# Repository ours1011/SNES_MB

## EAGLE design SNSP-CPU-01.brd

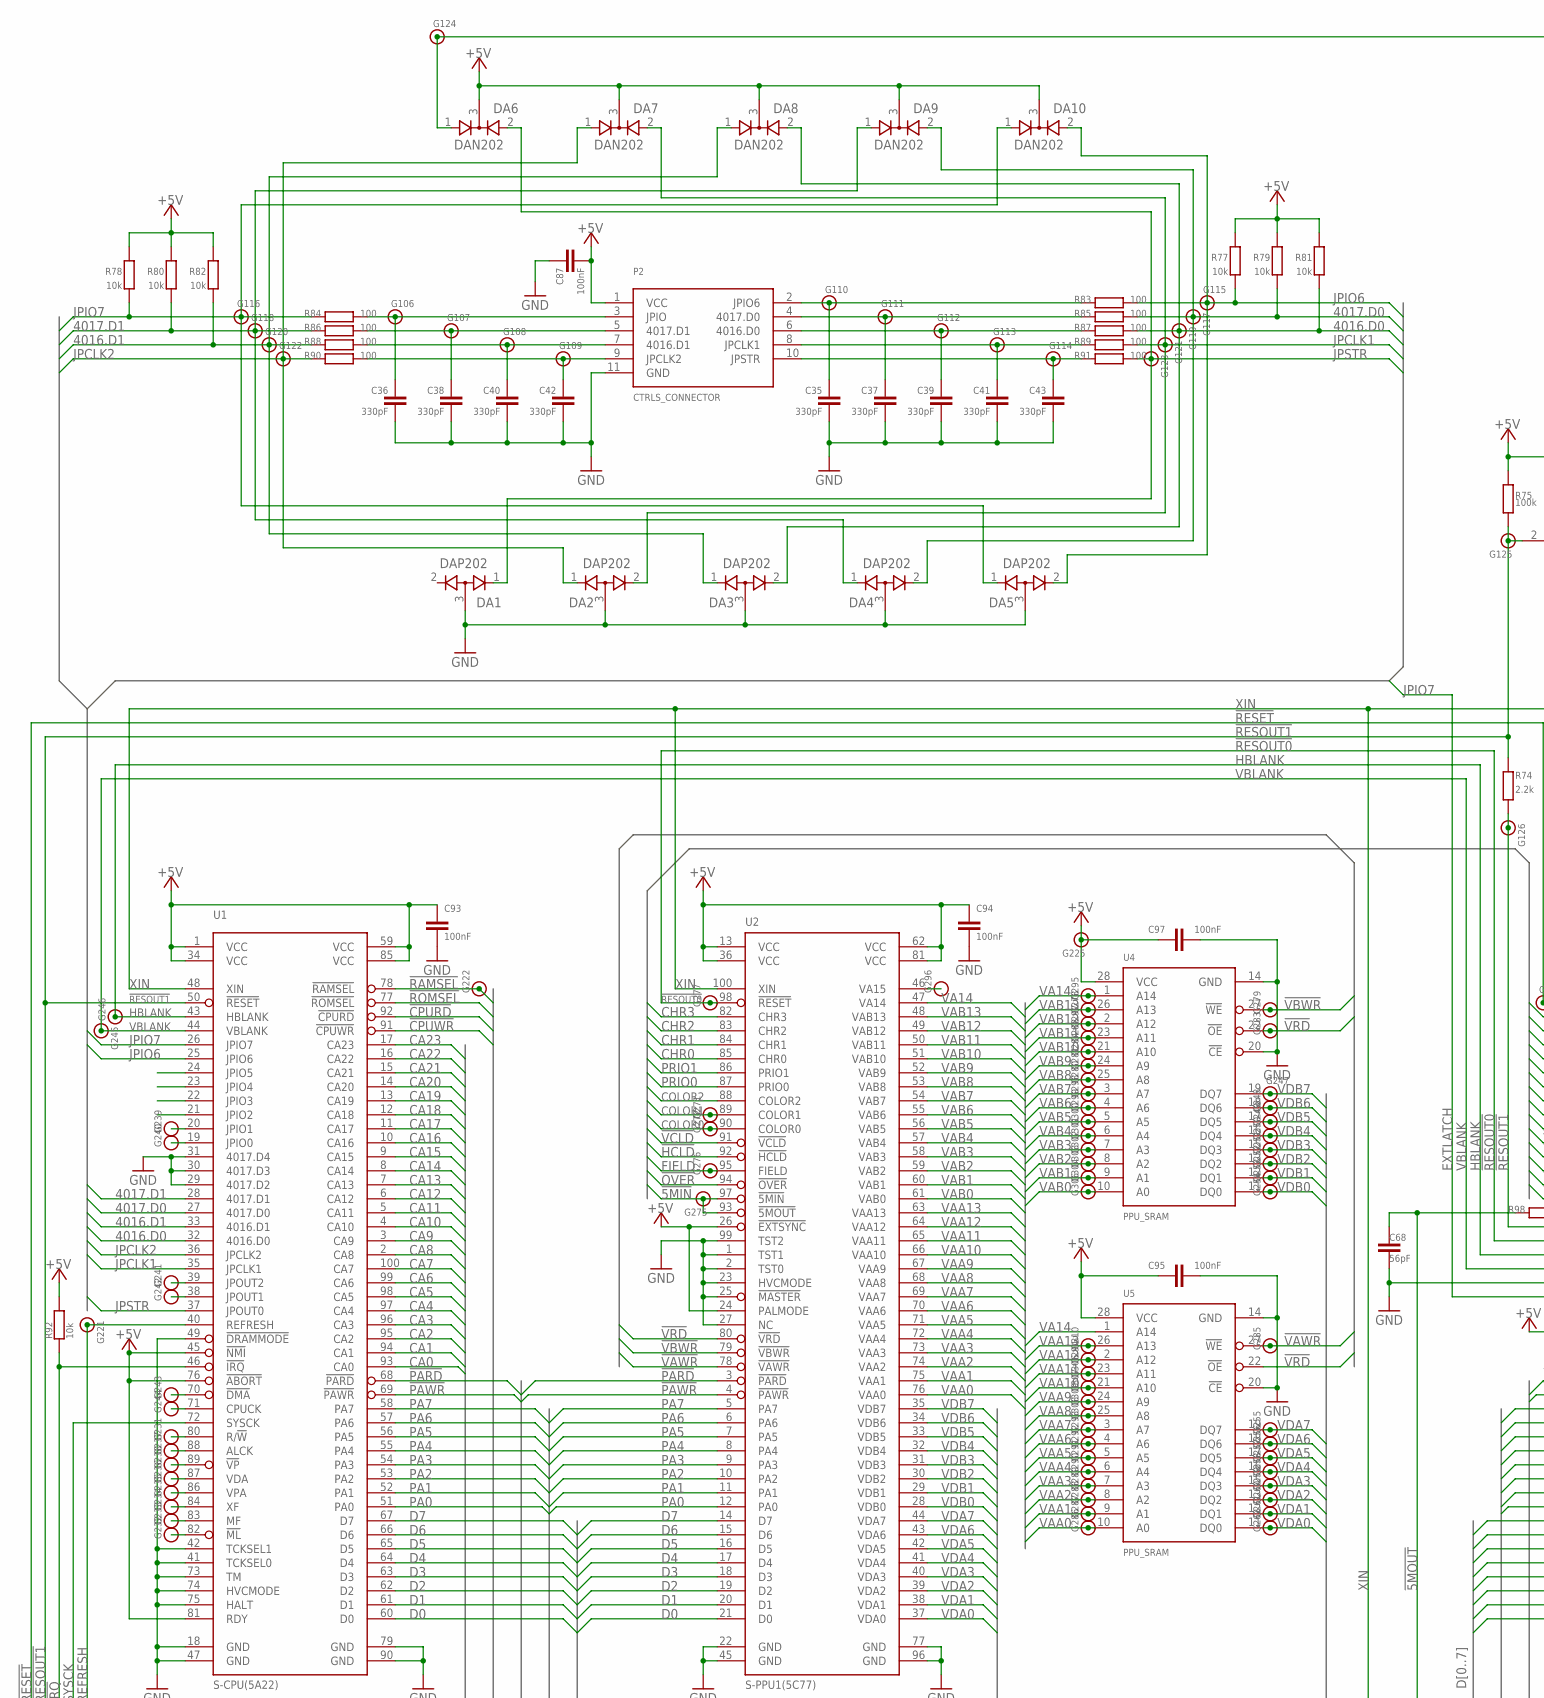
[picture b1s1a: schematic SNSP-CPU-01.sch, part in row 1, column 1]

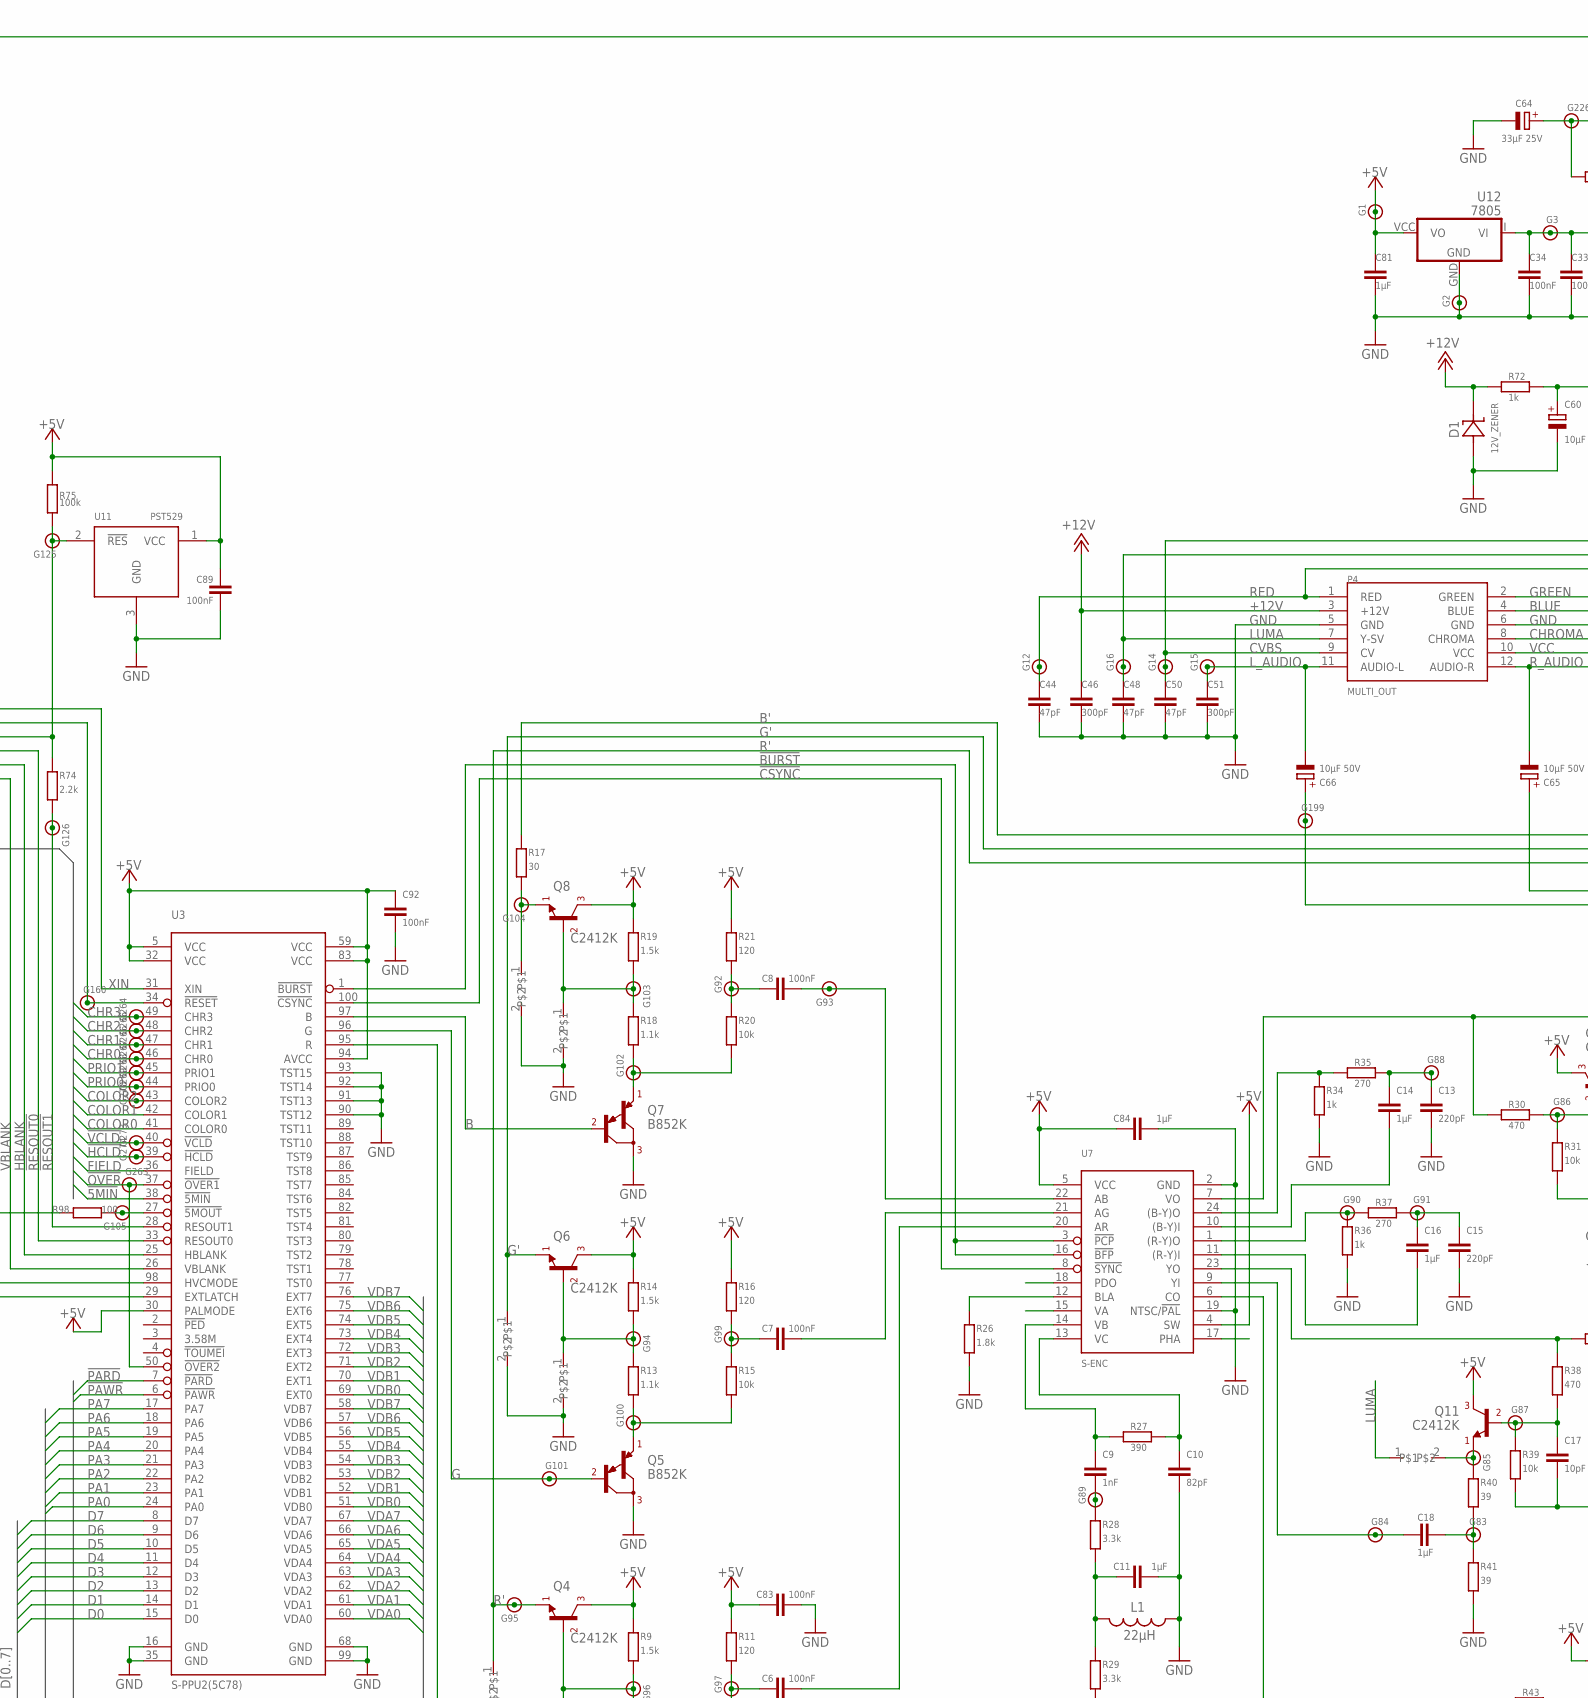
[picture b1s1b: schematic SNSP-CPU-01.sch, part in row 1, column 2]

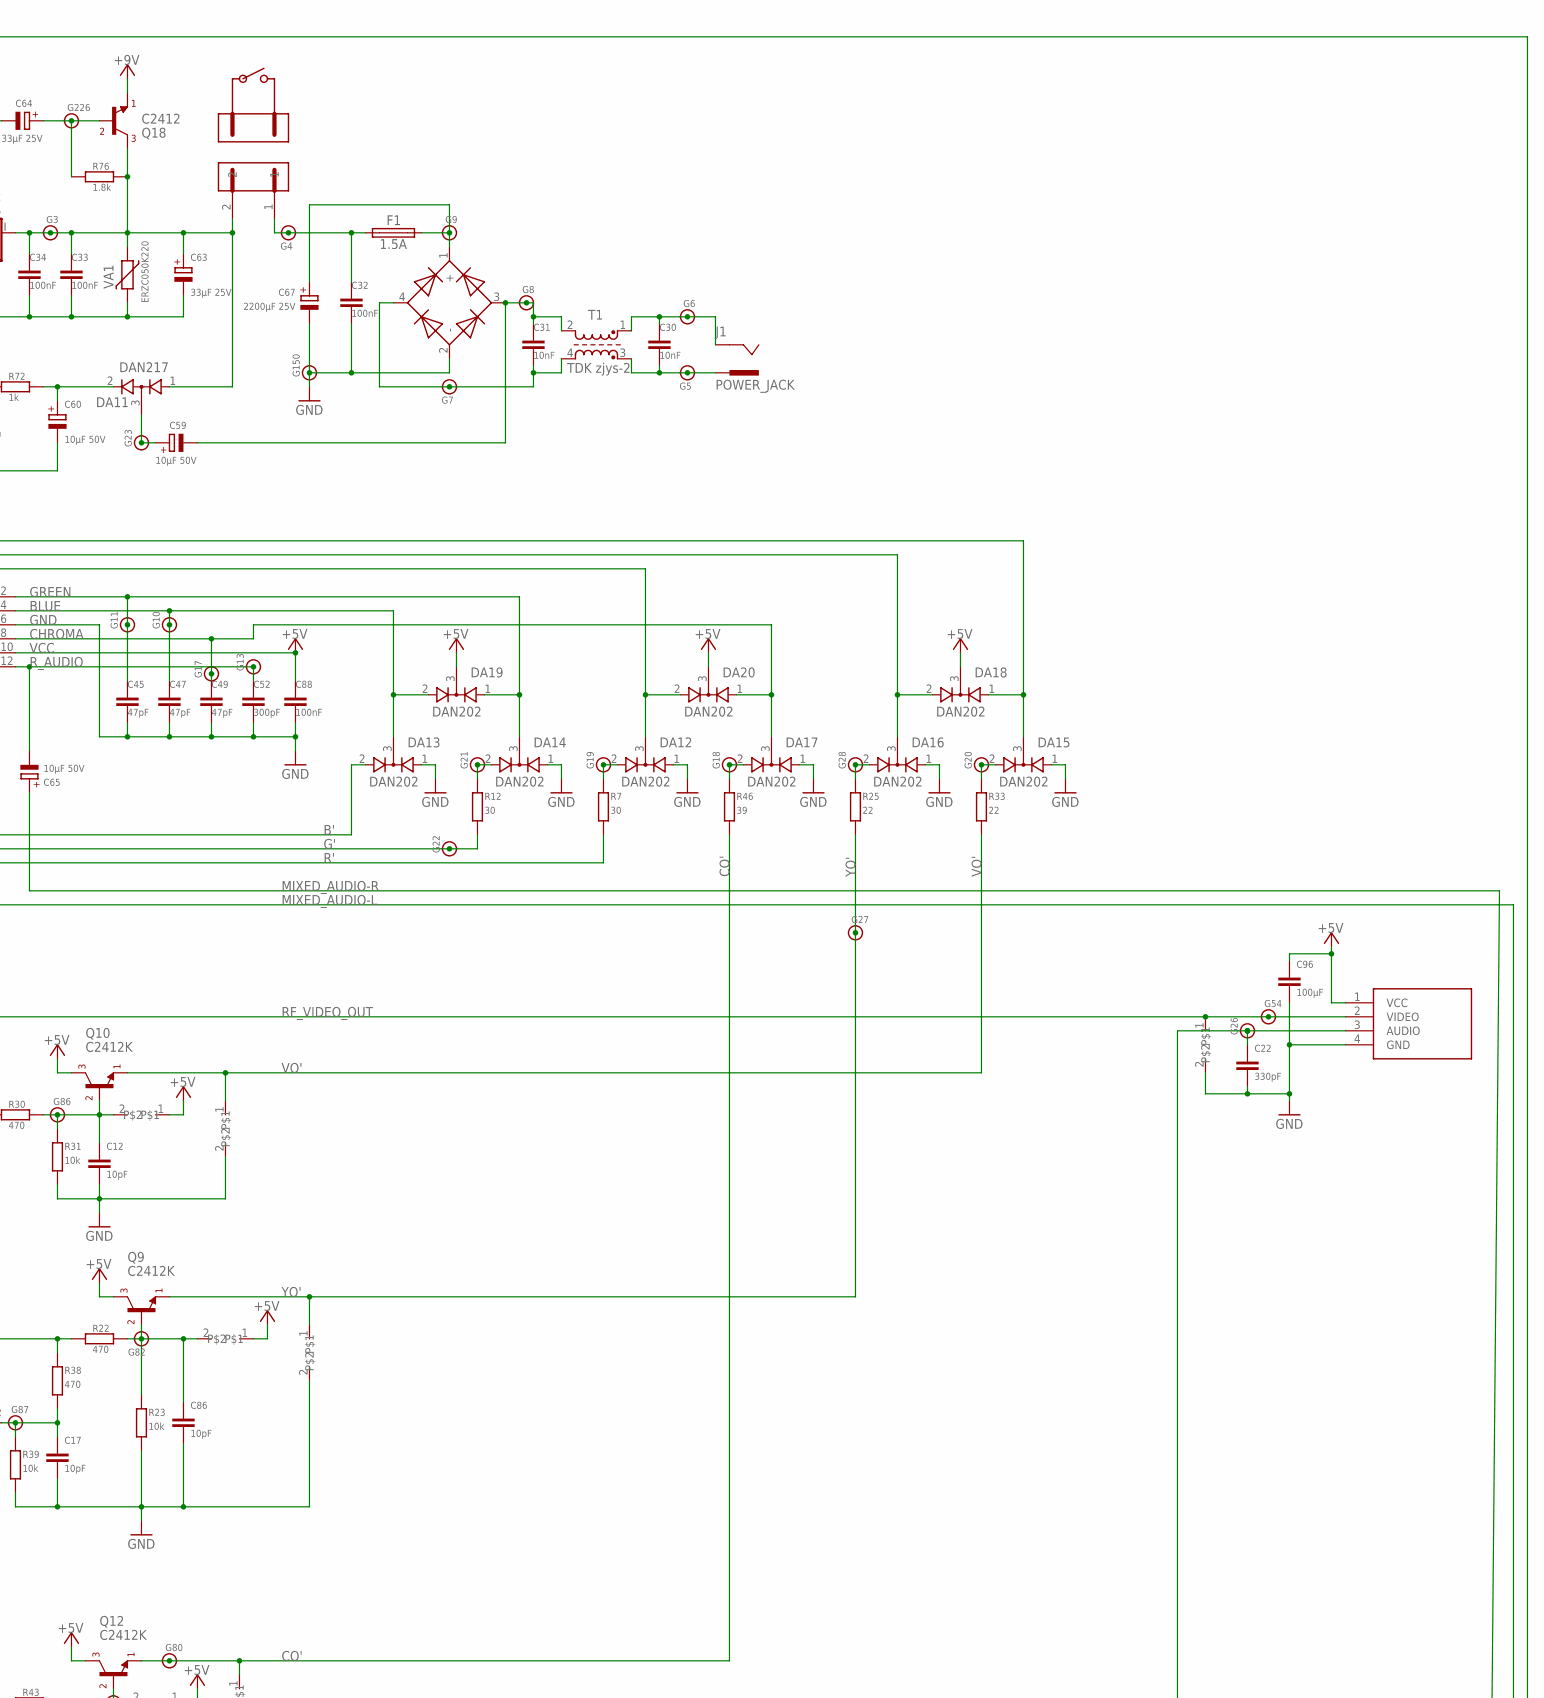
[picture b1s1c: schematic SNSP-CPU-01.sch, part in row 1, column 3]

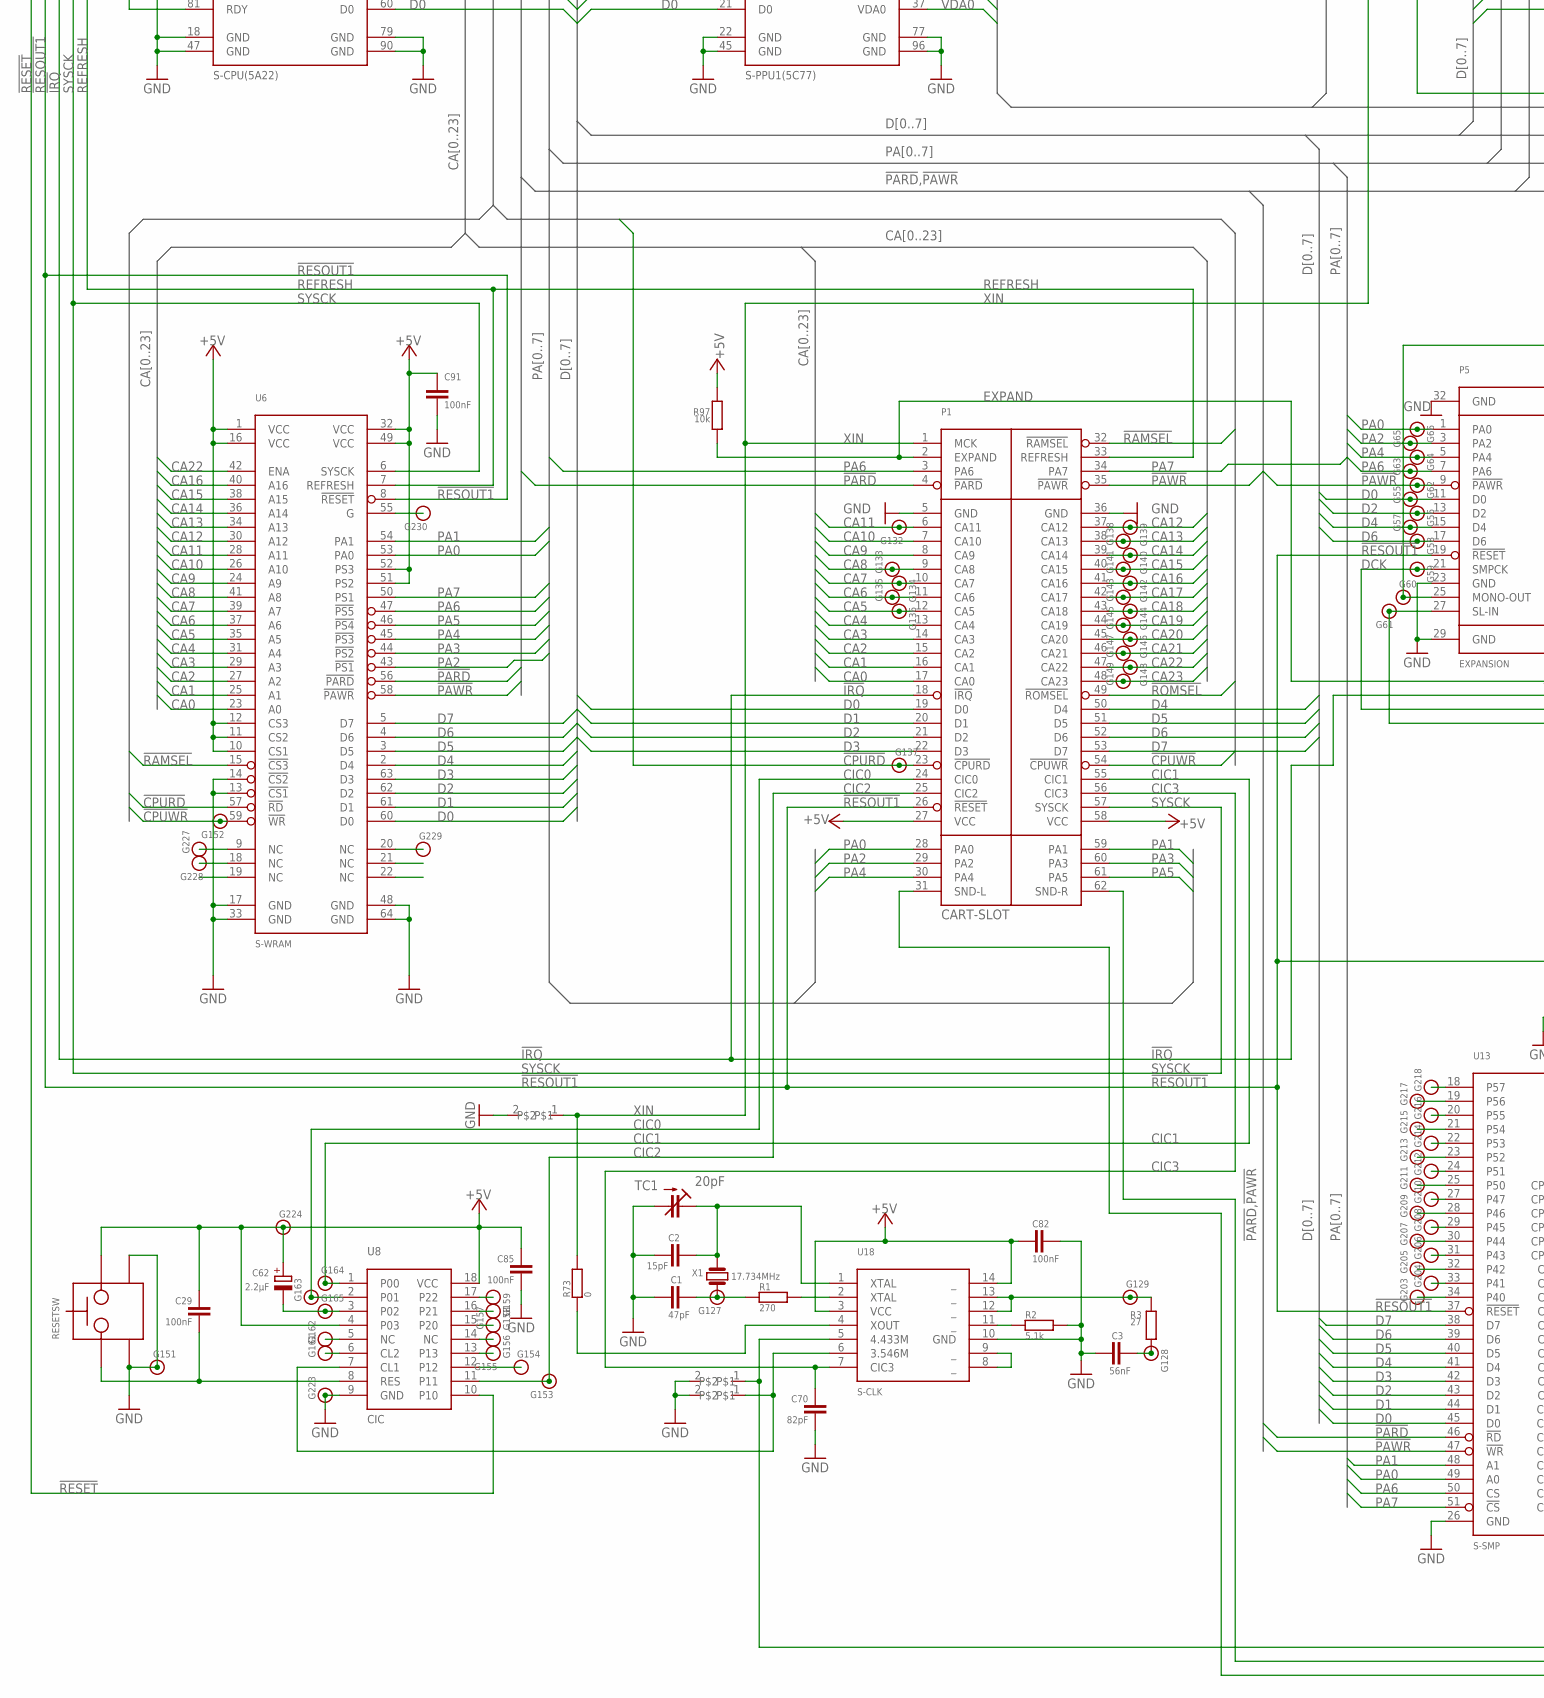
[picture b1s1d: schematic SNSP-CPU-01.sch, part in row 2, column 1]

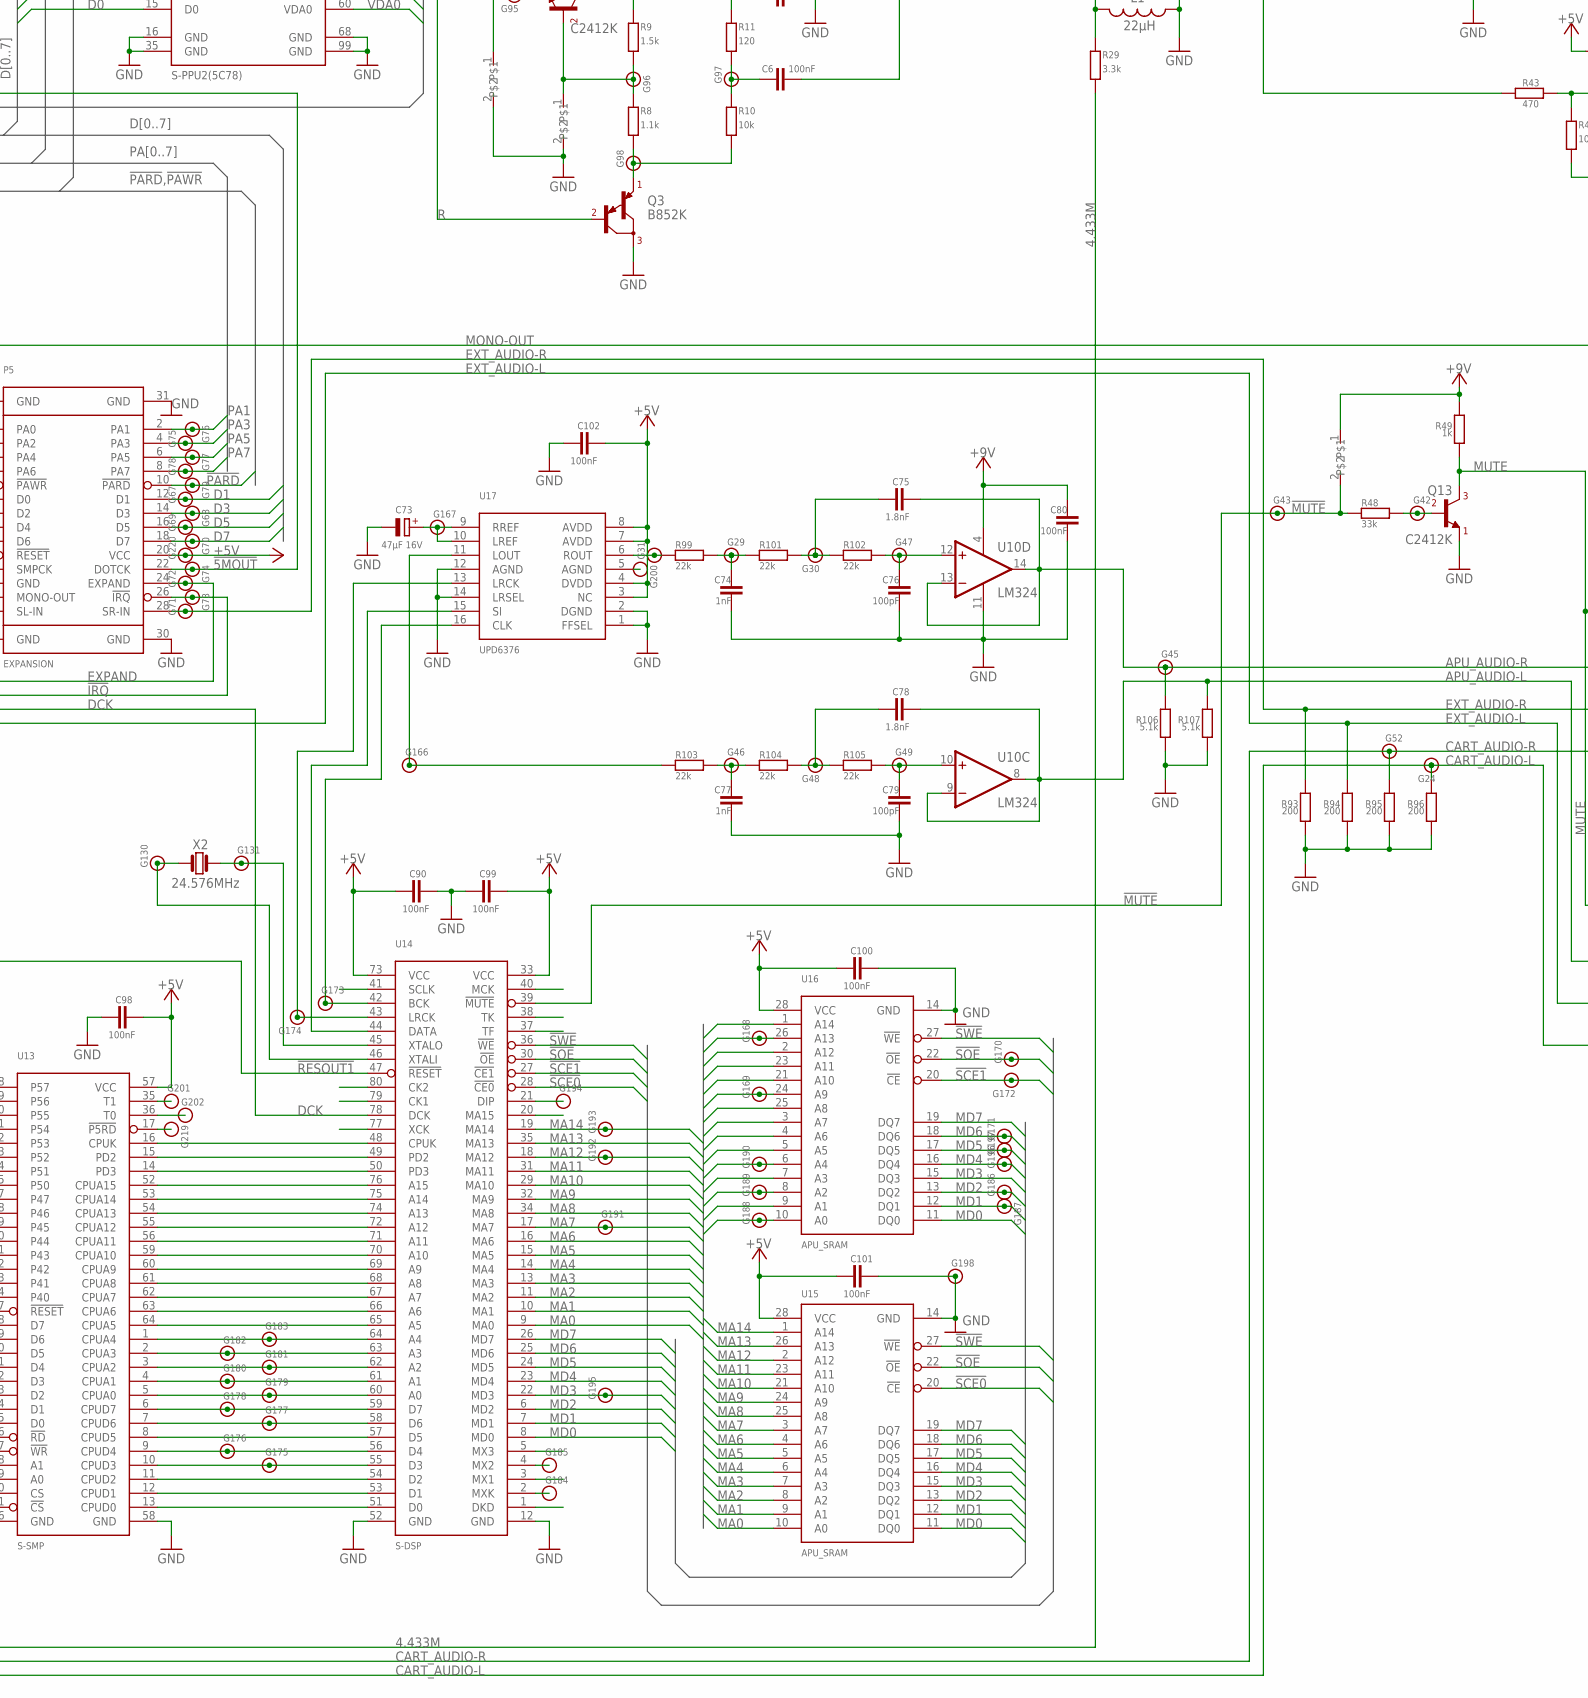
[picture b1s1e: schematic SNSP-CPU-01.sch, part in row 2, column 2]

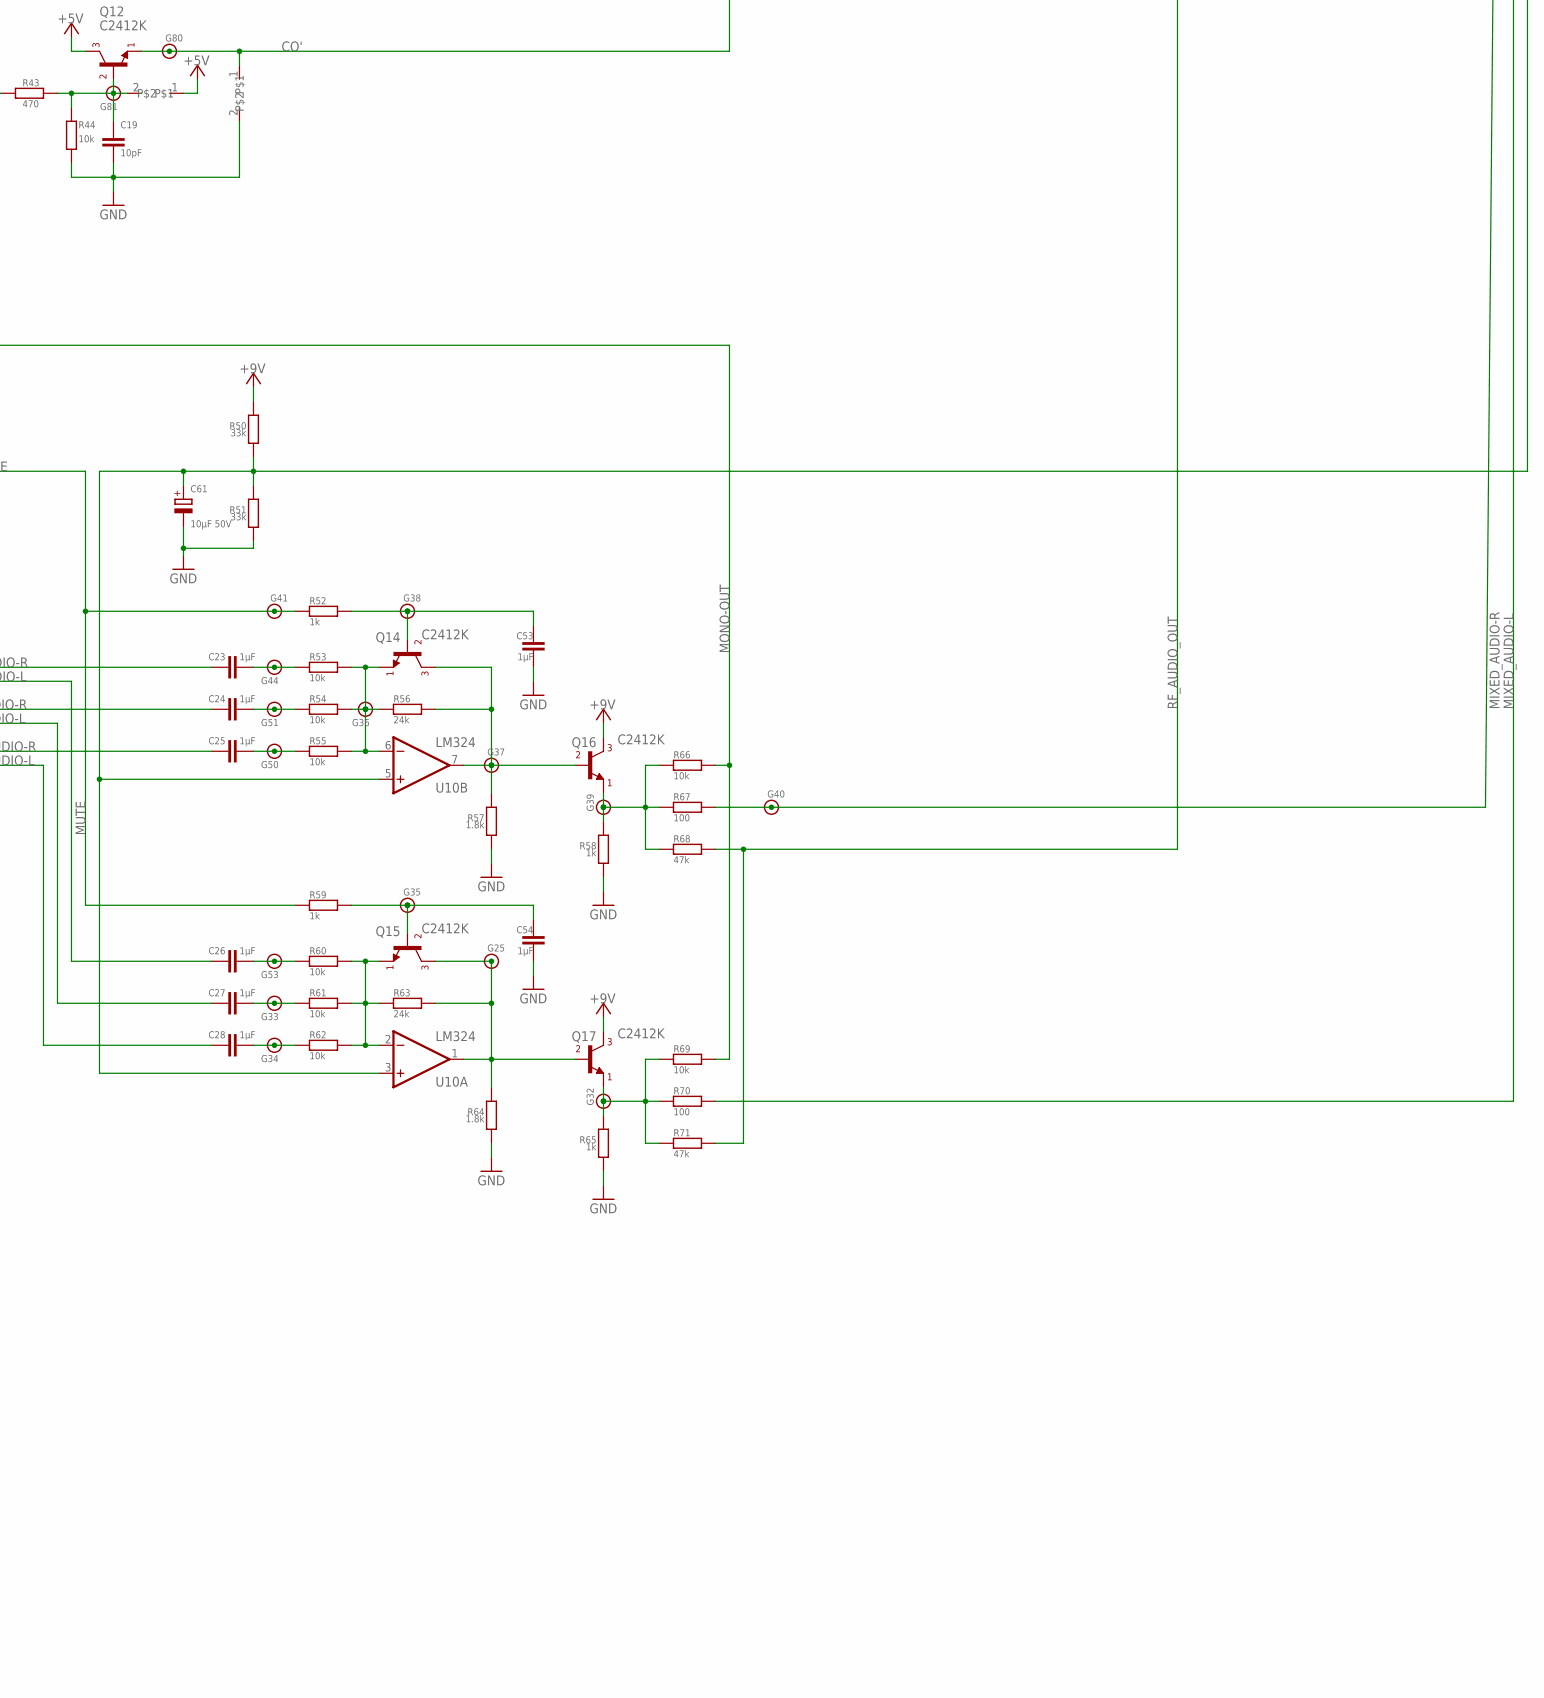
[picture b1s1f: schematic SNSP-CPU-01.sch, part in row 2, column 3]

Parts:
C1, C44, C45, C47, C48, C49, C50: 47pF; 0805
C2: 15pF; 0805
C3: 56nF; 0805
C4, C5, C69: EMPTY_0805; 0805_EMPTY
C6, C7, C8, C29, C32, C33, C34, C80, C82, C83, C85, C87, C88, C89, C90, C91, C92, C93, C94, C95, C97, C98, C99, C100, C101, C102: 100nF; 0805
C9, C74, C77: 1nF; 0805
C10, C70: 82pF; 0805
C11, C14, C16, C18, C23, C24, C25, C26, C27, C28, C53, C54, C81, C84: 1µF; 0805
C12, C17, C19, C86: 10pF; 0805
C13, C15: 220pF; 0805
C22, C35, C36, C37, C38, C39, C40, C41, C42, C43: 330pF; 0805
C30, C31: 10nF; 0805
C46, C51, C52: 300pF; 0805
C59, C60, C61, C65, C66: 10µF 50V; CAPA_POL_SMD_6.5
C62: 2.2µF; CAPA_POL_SMD_4.3
C63, C64: 33µF 25V; CAPA_POL_SMD_6.5
C67: 2200µF 25V; CAPA_POL
C68: 56pF; 0805
C73: 47µF 16V; CAPA_POL_SMD_6.5
C75, C78: 1.8nF; 0805
C76, C79: 100pF; 0805
C96: 100µF; 0805
D1: 12V_ZENER; SOT23
DA1, DA2, DA3, DA4, DA5: DAP202; SOT23
DA6, DA7, DA8, DA9, DA10, DA12, DA13, DA14, DA15, DA16, DA17, DA18, DA19, DA20: DAN202; SOT23
DA11: DAN217; SOT23
DB1: RECTIFIER
E1, E2, E3: EMPTY_0805; 0805_EMPTY
F1: 1.5A; FUSE
G1, G2, G3, G4, G5, G6, G7, G8, G9, G10, G11, G12, G13, G14, G15, G16, G17, G18, G19, G20, G21, G22, G23, G24, G25, G26, G27, G28, G29, G30, G31, G32, G33, G34, G35, G36, G37, G38, G39, G40, G41, G42, G43, G44, G45, G46, G47, G48, G49, G50, G51, G52, G53, G54, G55, G56, G57, G58, G59, G60, G61, G62, G63, G64, G65, G66, G67, G68, G69, G70, G71, G72, G73, G74, G75, G76, G77, G78, G79, G80, G81, G82, G83, G84, G85, G86, G87, G88, G89, G90, G91, G92, G93, G94, G95, G96, G97, G98, G99, G100, G101, G102, G103, G104, G105, G106, G107, G108, G109, G110, G111, G112, G113, G114, G115, G116, G117, G118, G119, G120, G121, G122, G123, G124, G125, G126, G127, G128, G129, G130, G131, G132, G133, G134, G135, G136, G137, G138, G139, G140, G141, G142, G143, G144, G145, G146, G147, G148, G149, G150, G151, G152, G153, G154, G155, G156, G157, G158, G159, G160, G161, G162, G163, G164, G165, G166, G167, G168, G169, G170, G171, G172, G173, G174, G175, G176, G177, G178, G179, G180, G181, G182, G183, G184, G185, G186, G187, G188, G189, G190, G191, G192, G193, G194, G195, G196, G197, G198, G199, G200, G201, G202, G203, G204, G205, G206, G207, G208, G209, G210, G211, G212, G213, G214, G215, G216, G217, G218, G219, G220, G221, G222, G223, G224, G225, G226, G227, G228, G229, G230, G231, G232, G233, G234, G235, G236, G237, G238, G239, G240, G241, G242, G243, G244, G245, G246, G247, G248, G249, G250, G251, G252, G253, G254, G255, G256, G257, G258, G259, G260, G261, G262, G263, G264, G265, G266, G267, G268, G269, G270, G271, G272, G273, G274, G275, G276, G277, G278, G279, G280, G281, G282, G283, G284, G285, G286, G287, G288, G289, G290, G291, G292, G293, G294, G295, G296, G297, G298, G299, G300, G301, G302, G303, G304, G305, G306, G307, G308, G309, G310: TEST
J1: POWER_JACK
J2: RF_MODULATOR; RF
L1: 22µH; INDUCTOR
P1: CART-SLOT
P2: CTRLS_CONNECTOR
P3: PWR_SW
P4: MULTI_OUT
P5: EXPANSION
Q3, Q5, Q7: B852K; SOT23
Q4, Q6, Q8, Q9, Q10, Q11, Q12, Q13, Q14, Q15, Q16, Q17: C2412K; SOT23
Q18: C2412; SOT23
R1, R35, R37: 270; 0805
R2, R106, R107: 5.1k; 0805
R3: 27; 0805
R4, R5, R6, R24, R32, R42, R45, R47, R108, R109, R110, R111: EMPTY_0805; 0805_EMPTY
R7, R12, R17: 30; 0805
R8, R13, R18: 1.1k; 0805
R9, R14, R19: 1.5k; 0805
R10, R15, R20, R23, R31, R39, R44, R53, R54, R55, R60, R61, R62, R66, R69, R77, R78, R79, R80, R81, R82, R92, R97: 10k; 0805
R11, R16, R21: 120; 0805
R22, R30, R38, R43: 470; 0805
R25, R33: 22; 0805
R26, R57, R64, R76: 1.8k; 0805
R27: 390; 0805
R28, R29: 3.3k; 0805
R34, R36, R49, R52, R58, R59, R65, R72: 1k; 0805
R40, R41, R46: 39; 0805
R48, R50, R51: 33k; 0805
R56, R63: 24k; 0805
R67, R70, R83, R84, R85, R86, R87, R88, R89, R90, R91, R98: 100; 0805
R68, R71: 47k; 0805
R73: 0; 0805
R74: 2.2k; 0805
R75: 100k; 0805
R93, R94, R95, R96: 200; 0805
R99, R101, R102, R103, R104, R105: 22k; 0805
RESETSW: RESET_SW
T1: TDK zjys-2; TRANSF
TC1: 20pF; C-TRIMM
U1: S-CPU(5A22); 100QFP0.65
U2: S-PPU1(5C77); 100QFP0.65
U3: S-PPU2(5C78); 100QFP0.65
U4, U5: PPU_SRAM; SO28L
U6: S-WRAM; SSO64
U7: S-ENC; SO24
U8: CIC
U10: LM324; SO14
U11: PST529
U12: 7805; TO220V
U13: S-SMP; 64QFP1.00
U14: S-DSP; 80QFP0.8
U15, U16: APU_SRAM; SO28W
U17: UPD6376; SO16
U18: S-CLK; SO14L
VA1: ERZC050K220; VARISTOR
X1: 17.734MHz; XTAL_MAIN
X2: 24.576MHz; XTAL_S-DSP

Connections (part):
4.433M: C69.1, R29.1, U18.5 (4.433M)
4016.D0: DA3.2, DA8.2 (1), G119.T, R81.1, R87.2, U1.32 (4016.D0)
4016.D1: DA3.1, DA8.1 (2), G120.T, R82.1, R88.1, U1.33 (4016.D1)
4017.D0: DA4.2, DA9.2 (1), G117.T, R79.1, R85.2, U1.27 (4017.D0)
4017.D1: DA4.1, DA9.1 (2), G118.T, R80.1, R86.1, U1.28 (4017.D1)
!5MIN: G275.T, U2.93 (!5MOUT), U2.97 (!5MIN), U3.38 (!5MIN)
!5MOUT: C68.1, G74.T, P5.22 (DOTCK), R98.1
!BURST: U3.1 (!BURST), U7.3 (!PCP), U7.16 (!BFP)
!CPURD: G137.T, P1.23 (!CPURD), U1.92 (!CPURD), U6.57 (!RD)
!CPUWR: G152.T, P1.54 (!CPUWR), U1.91 (!CPUWR), U6.59 (!WR)
!CSYNC: U3.100 (!CSYNC), U7.8 (!SYNC)
!HCLD: G274.T, U2.92 (!HCLD), U3.39 (!HCLD)
!IRQ: G73.T, P1.18 (!IRQ), P5.26 (!IRQ), R92.1, U1.46 (!IRQ)
!MUTE: G43.T, R47.2, R48.1, U14.39 (!MUTE)
!OVER: G263.T, U2.94 (!OVER), U3.37 (!OVER1), U3.50 (!OVER2)
!PARD: G79.T, P1.4 (!PARD), P5.10 (!PARD), U1.68 (!PARD), U2.3 (!PARD), U3.7 (!PARD), U6.56 (!PARD), U13.46 (!RD)
!PAWR: G62.T, P1.35 (!PAWR), P5.9 (!PAWR), U1.69 (!PAWR), U2.4 (!PAWR), U3.6 (!PAWR), U6.58 (!PAWR), U13.47 (!WR)
!RAMSEL: G222.T, P1.32 (!RAMSEL), U1.78 (!RAMSEL), U6.15 (!CS3)
!RESET: G160.T, U3.34 (!RESET), U8.10
!RESOUT0: G277.T, U2.98 (!RESET), U3.33 (RESOUT0)
!RESOUT1: G125.T, P1.26 (!RESET), P5.19 (!RESET), R74.2, R75.1, U1.50 (!RESET), U6.8 (!RESET), U11.2 (!RES), U13.37 (!RESET), U14.47 (!RESET)
!ROMSEL: P1.49 (!ROMSEL), U1.77 (!ROMSEL)
!SCE0: U14.28 (!CE0), U15.20 (!CE)
!SCE1: G172.T, U14.27 (!CE1), U16.20 (!CE)
!SOE: G170.T, U14.30 (!OE), U15.22 (!OE), U16.22 (!OE)
!SWE: U14.36 (!WE), U15.27 (!WE), U16.27 (!WE)
!VAWR: G285.T, U2.78 (!VAWR), U5.27 (!WE)
!VBWR: G279.T, U2.79 (!VBWR), U4.27 (!WE)
!VCLD: G273.T, U2.91 (!VCLD), U3.40 (!VCLD)
!VRD: G283.T, U2.80 (!VRD), U4.22 (!OE), U5.22 (!OE)
+9V: C80.2, Q16.3, Q17.3, Q18.2 (1), R47.1, R49.1, R50.1, U10.4 (V+)
+12V: C46.2, D1.3, P4.3 (+12V), R72.2
/RESOUT1: G126.T, R74.1, U3.28 (RESOUT1)
APU_AUDIO-L: C26.1, C78.2, R107.1, U10.8 (OUT), U10.9 (-IN)
APU_AUDIO-R: C23.1, C75.2, G45.T, R106.1, U10.13 (-IN), U10.14 (OUT)
B: Q7.1 (2), U3.97 (B)
B': DA13.2 (1), R17.2
BLUE: C47.2, DA13.3, DA19.2 (1), G10.T, P4.4 (BLUE)
CA0: P1.17 (CA0), U1.93 (CA0), U6.23 (A0)
CA1: P1.16 (CA1), U1.94 (CA1), U6.25 (A1)
CA2: P1.15 (CA2), U1.95 (CA2), U6.27 (A2)
CA3: P1.14 (CA3), U1.96 (CA3), U6.29 (A3)
CA4: P1.13 (CA4), U1.97 (CA4), U6.31 (A4)
CA5: G136.T, P1.12 (CA5), U1.98 (CA5), U6.35 (A5)
CA6: G135.T, P1.11 (CA6), U1.99 (CA6), U6.37 (A6)
CA7: G134.T, P1.10 (CA7), U1.100 (CA7), U6.39 (A7)
CA8: G133.T, P1.9 (CA8), U1.2 (CA8), U6.41 (A8)
CA9: P1.8 (CA9), U1.3 (CA9), U6.24 (A9)
CA10: P1.7 (CA10), U1.4 (CA10), U6.26 (A10)
CA11: G132.T, P1.6 (CA11), U1.5 (CA11), U6.28 (A11)
CA12: G139.T, P1.37 (CA12), U1.6 (CA12), U6.30 (A12)
CA13: G138.T, P1.38 (CA13), U1.7 (CA13), U6.34 (A13)
CA14: G140.T, P1.39 (CA14), U1.8 (CA14), U6.36 (A14)
CA15: G141.T, P1.40 (CA15), U1.9 (CA15), U6.38 (A15)
CA16: G142.T, P1.41 (CA16), U1.10 (CA16), U6.40 (A16)
CA17: G143.T, P1.42 (CA17), U1.11 (CA17)
CA18: G144.T, P1.43 (CA18), U1.12 (CA18)
CA19: G145.T, P1.44 (CA19), U1.13 (CA19)
CA20: G146.T, P1.45 (CA20), U1.14 (CA20)
CA21: G147.T, P1.46 (CA21), U1.15 (CA21)
CA22: G148.T, P1.47 (CA22), U1.16 (CA22), U6.42 (ENA)
CA23: G149.T, P1.48 (CA23), U1.17 (CA23)
CART_AUDIO-L: C28.1, G24.T, P1.31 (SND-L), R96.1
CART_AUDIO-R: C25.1, G52.T, P1.62 (SND-R), R95.1
CHR0: G267.T, U2.85 (CHR0), U3.46 (CHR0)
CHR1: G266.T, U2.84 (CHR1), U3.47 (CHR1)
CHR2: G265.T, U2.83 (CHR2), U3.48 (CHR2)
CHR3: G264.T, U2.82 (CHR3), U3.49 (CHR3)
CHROMA: C49.2, DA17.3, DA20.1 (2), G17.T, P4.8 (CHROMA)
CIC0: G163.T, P1.24 (CIC0), U8.2 (P01)
CIC1: G164.T, P1.55 (CIC1), U8.1 (P00)
CIC2: G153.T, P1.25 (CIC2), U8.11
CIC3: C70.1, P1.56 (CIC3), U18.7 (CIC3)
CO': G80.T, Q12.2 (1), R45.1, R46.1
COLOR0: G272.T, U2.90 (COLOR0), U3.41 (COLOR0)
COLOR1: G271.T, U2.89 (COLOR1), U3.42 (COLOR1)
COLOR2: G270.T, U2.88 (COLOR2), U3.43 (COLOR2)
CVBS: C50.2, DA15.3, DA18.1 (2), G14.T, P4.9 (CV)
D0: G55.T, P1.19 (D0), P5.11 (D0), U1.60 (D0), U2.21 (D0), U3.15 (D0), U6.60 (D0), U13.45 (D0)
D1: G67.T, P1.20 (D1), P5.12 (D1), U1.61 (D1), U2.20 (D1), U3.14 (D1), U6.61 (D1), U13.44 (D1)
D2: G56.T, P1.21 (D2), P5.13 (D2), U1.62 (D2), U2.19 (D2), U3.13 (D2), U6.62 (D2), U13.43 (D2)
D3: G68.T, P1.22 (D3), P5.14 (D3), U1.63 (D3), U2.18 (D3), U3.12 (D3), U6.63 (D3), U13.42 (D3)
D4: G57.T, P1.50 (D4), P5.15 (D4), U1.64 (D4), U2.17 (D4), U3.11 (D4), U6.2 (D4), U13.41 (D4)
D5: G69.T, P1.51 (D5), P5.16 (D5), U1.65 (D5), U2.16 (D5), U3.10 (D5), U6.3 (D5), U13.40 (D5)
D6: G58.T, P1.52 (D6), P5.17 (D6), U1.66 (D6), U2.15 (D6), U3.9 (D6), U6.4 (D6), U13.39 (D6)
D7: G70.T, P1.53 (D7), P5.18 (D7), U1.67 (D7), U2.14 (D7), U3.8 (D7), U6.5 (D7), U13.38 (D7)
DCK: G59.T, P5.21 (SMPCK), U14.78 (DCK)
EXPAND: G72.T, P1.2 (EXPAND), P5.24 (EXPAND), R97.1
EXT_AUDIO-L: C27.1, G61.T, P5.27 (SL-IN), R94.1
EXT_AUDIO-R: C24.1, G71.T, P5.28 (SR-IN), R93.1
FIELD: G276.T, U2.95 (FIELD), U3.36 (FIELD)
G: G101.T, Q5.1 (2), U3.96 (G)
G': G22.T, Q6.2 (1), R5.1, R12.1
GND: C1.2, C2.2, C3.1, C4.2, C5.2, C10.2, C11.2, C12.2, C13.1, C15.1, C17.2, C19.2, C22.2, C32.1, C33.1, C34.1, C35.2, C36.2, C37.2, C38.2, C39.2, C40.2, C41.2, C42.2, C43.2, C44.1, C45.1, C46.1, C47.1, C48.1, C49.1, C50.1, C51.1, C52.1, C53.1, C54.1, C60.-, C61.-, C63.-, C64.-, C67.-, C68.2, C69.2, C70.2, C73.-, C74.1, C76.1, C77.1, C79.1, C80.1, C81.1, C82.2, C83.2, C84.2, C85.2, C86.2, C87.1, C88.1, C89.2, C90.2, C91.2, C92.2, C93.2, C94.2, C95.2, C96.2, C97.2, C98.1, C99.1, C100.2, C101.2, C102.1, D1.1, DA1.3, DA2.3, DA3.3, DA4.3, DA5.3, DA12.1 (2), DA13.1 (2), DA14.1 (2)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
GREEN: C45.2, DA14.3, DA19.1 (2), G11.T, P4.2 (GREEN)
HBLANK: G246.T, U1.43 (HBLANK), U3.25 (HBLANK)
JPCLK1: DA2.2, DA7.2 (1), G121.T, R89.2, U1.35 (JPCLK1)
JPCLK2: DA2.1, DA7.1 (2), G122.T, R90.1, U1.36 (JPCLK2)
JPIO6: DA5.2, DA10.2 (1), G115.T, R77.1, R83.2, U1.25 (JPIO6)
JPIO7: DA5.1, DA10.1 (2), G116.T, R78.1, R84.1, U1.26 (JPIO7), U3.29 (EXTLATCH)
JPSTR: DA1.1, DA6.2 (1), G123.T, R91.2, U1.37 (JPOUT0)
LUMA: C48.2, DA16.3, DA18.2 (1), G16.T, P4.7 (Y-SV), R42.1
L_AUDIO: C51.2, C66.-, G15.T, P4.11 (AUDIO-L)
MA0: G188.T, U14.9 (MA0), U15.10 (A0), U16.10 (A0)
MA1: U14.10 (MA1), U15.9 (A1), U16.9 (A1)
MA2: G189.T, U14.11 (MA2), U15.8 (A2), U16.8 (A2)
MA3: U14.13 (MA3), U15.7 (A3), U16.7 (A3)
MA4: G190.T, U14.14 (MA4), U15.6 (A4), U16.6 (A4)
MA5: U14.15 (MA5), U15.5 (A5), U16.5 (A5)
MA6: U14.16 (MA6), U15.4 (A6), U16.4 (A6)
MA7: G191.T, U14.17 (MA7), U15.3 (A7), U16.3 (A7)
MA8: U14.34 (MA8), U15.25 (A8), U16.25 (A8)
MA9: G169.T, U14.32 (MA9), U15.24 (A9), U16.24 (A9)
MA10: U14.29 (MA10), U15.21 (A10), U16.21 (A10)
MA11: U14.31 (MA11), U15.23 (A11), U16.23 (A11)
MA12: G192.T, U14.18 (MA12), U15.2 (A12), U16.2 (A12)
MA13: G168.T, U14.35 (MA13), U15.26 (A13), U16.26 (A13)
MA14: G193.T, U14.19 (MA14), U15.1 (A14), U16.1 (A14)
MA15: U14.20 (MA15)
MD0: U14.8 (MD0), U15.11 (DQ0), U16.11 (DQ0)
MD1: G187.T, U14.7 (MD1), U15.12 (DQ1), U16.12 (DQ1)
MD2: G186.T, U14.6 (MD2), U15.13 (DQ2), U16.13 (DQ2)
MD3: G195.T, U14.22 (MD3), U15.15 (DQ3), U16.15 (DQ3)
MD4: G196.T, U14.23 (MD4), U15.16 (DQ4), U16.16 (DQ4)
MD5: G197.T, U14.24 (MD5), U15.17 (DQ5), U16.17 (DQ5)
MD6: G171.T, U14.25 (MD6), U15.18 (DQ6), U16.18 (DQ6)
MD7: U14.26 (MD7), U15.19 (DQ7), U16.19 (DQ7)
MIXED_AUDIO-L: C66.+, G199.T, R70.2
MIXED_AUDIO-R: C65.+, G40.T, R67.2
MONO-OUT: G60.T, P5.25 (MONO-OUT), R66.2, R69.2
MUTE: G41.T, Q13.3, R49.2, R52.1, R59.1
unnamed: C4.1, U8.7 (CL1), U18.6 (3.546M)
unnamed: R1.2, U18.2 (XTAL)
unnamed: C62.-, G165.T, U8.3 (P02)
unnamed: C29.2, RESETSW.2 (1), U8.8 (RES)
unnamed: R73.1, U18.4 (XOUT)
unnamed: C36.1, G106.T, P2.3 (JPIO), R84.2
unnamed: C1.1, G127.T, R1.1, X1.P$1
unnamed: C38.1, G107.T, P2.5 (4017.D1), R86.2
unnamed: R2.1, U18.11 (_)
unnamed: C2.1, TC1.+, U18.1 (XTAL), X1.P$2
unnamed: G129.T, R3.1, U18.12 (_), U18.13 (_)
unnamed: C40.1, G108.T, P2.7 (4016.D1), R88.2
unnamed: U18.8 (_), U18.9 (_)
unnamed: C42.1, G109.T, P2.9 (JPCLK2), R90.2
unnamed: C35.1, G110.T, P2.2 (JPIO6), R83.1
unnamed: C37.1, G111.T, P2.4 (4017.D0), R85.1
unnamed: C39.1, G112.T, P2.6 (4016.D0), R87.1
unnamed: C41.1, G113.T, P2.8 (JPCLK1), R89.1
unnamed: C43.1, G114.T, P2.10 (JPSTR), R91.1
unnamed: C61.+, DA6.1 (2), G124.T, R50.2, R51.1, U10.3 (+IN), U10.5 (+IN)
unnamed: G105.T, R98.2, U3.27 (!5MOUT)
unnamed: E1.1, G96.T, Q4.1 (2), R8.2, R9.1
unnamed: C6.1, G97.T, R10.2, R11.1
unnamed: G98.T, Q3.2 (1), R8.1, R10.1
unnamed: E2.1, G94.T, Q6.1 (2), R13.2, R14.1
unnamed: C6.2, U7.20 (AR)
unnamed: C7.1, G99.T, R15.2, R16.1
unnamed: G100.T, Q5.2 (1), R13.1, R15.1
unnamed: C7.2, U7.21 (AG)
unnamed: E3.1, G103.T, Q8.1 (2), R18.2, R19.1
unnamed: C8.1, G92.T, R20.2, R21.1
unnamed: G102.T, Q7.2 (1), R18.1, R20.1
unnamed: C8.2, G93.T, U7.22 (AB)
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
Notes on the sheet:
!RESOUT1
EXTLATCH
